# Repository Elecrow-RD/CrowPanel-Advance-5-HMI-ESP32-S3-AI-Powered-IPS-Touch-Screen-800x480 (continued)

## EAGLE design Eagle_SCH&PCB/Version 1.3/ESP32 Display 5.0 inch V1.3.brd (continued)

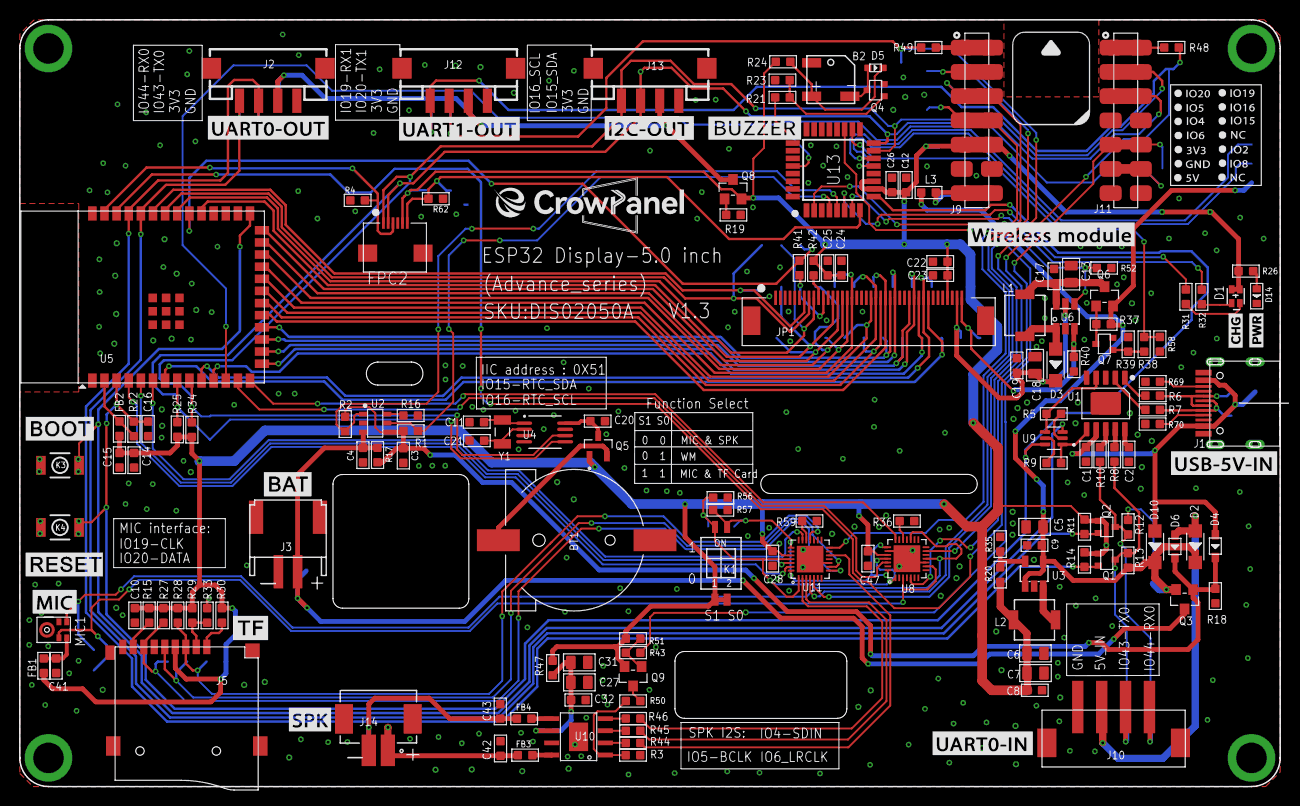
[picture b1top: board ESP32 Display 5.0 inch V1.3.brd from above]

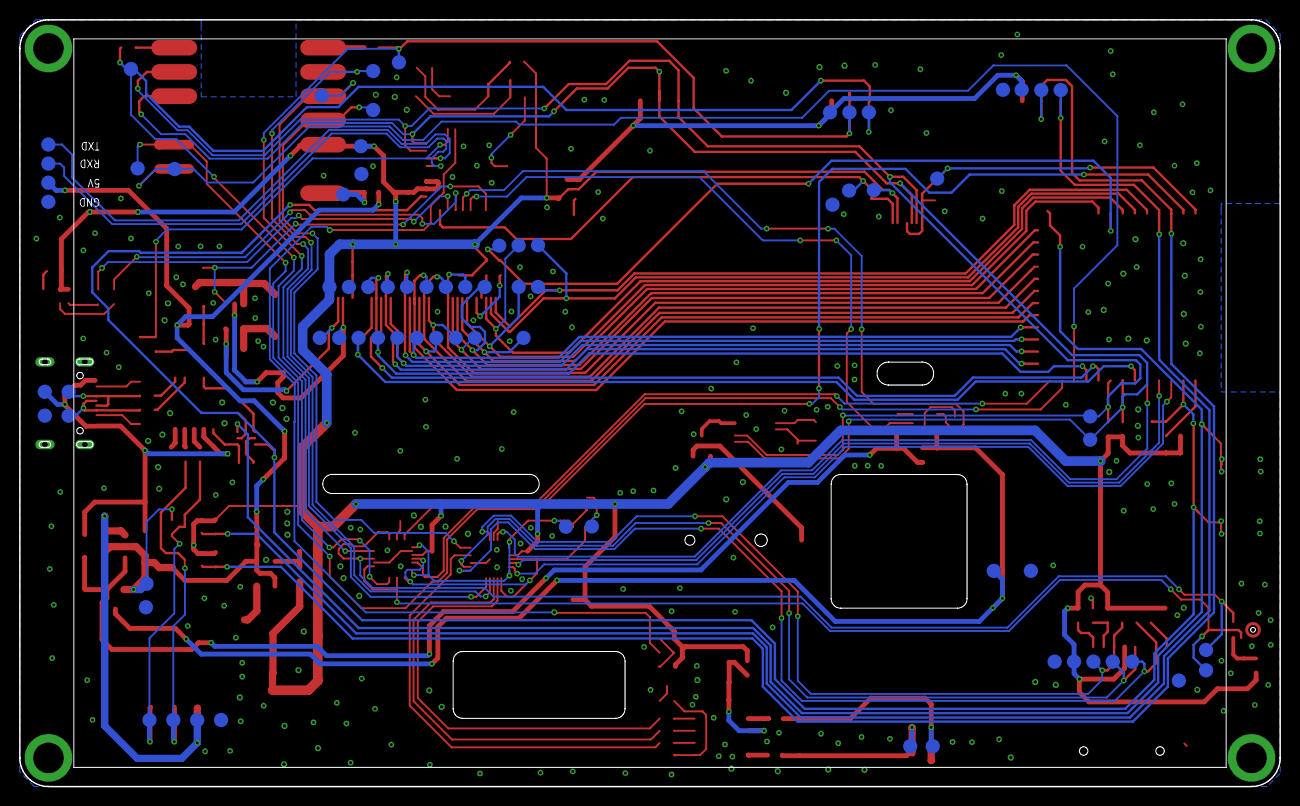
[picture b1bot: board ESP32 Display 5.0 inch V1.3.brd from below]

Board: 2 copper layers, 132.0 x 80.3 mm, 223 parts (72 on the bottom side), 126 nets.

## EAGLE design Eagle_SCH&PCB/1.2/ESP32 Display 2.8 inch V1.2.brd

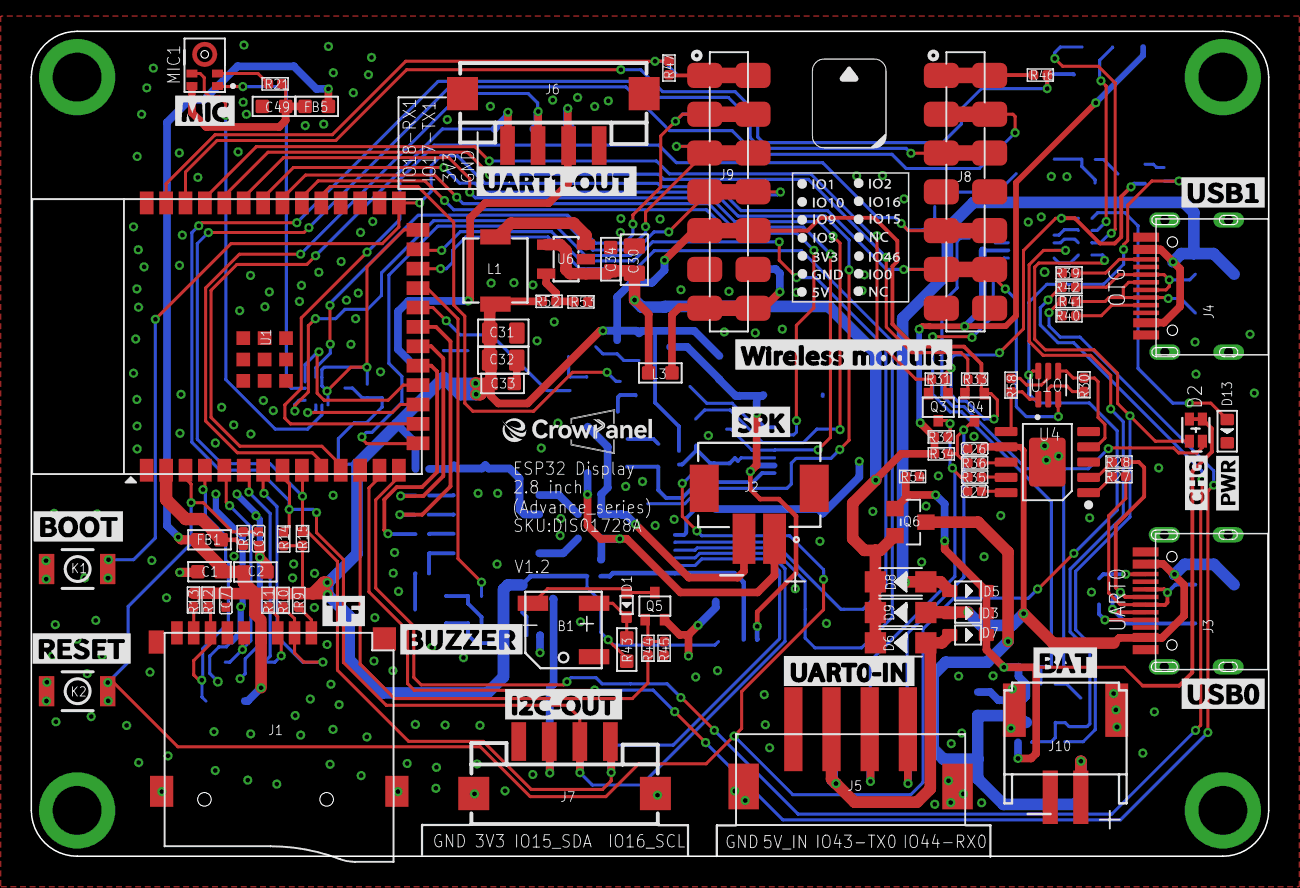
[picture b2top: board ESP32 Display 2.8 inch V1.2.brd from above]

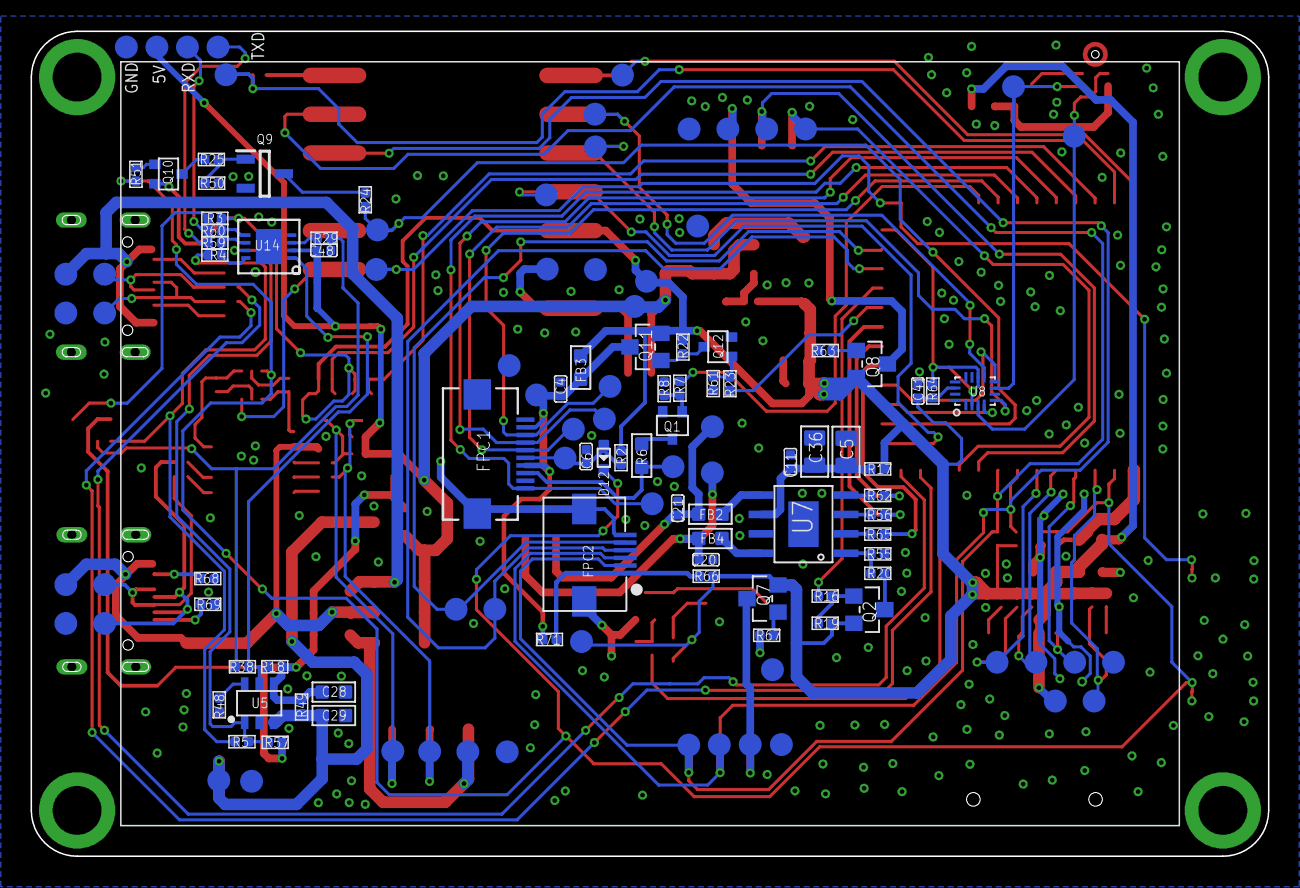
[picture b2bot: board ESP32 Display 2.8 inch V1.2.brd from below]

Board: 2 copper layers, 81.0 x 54.0 mm, 205 parts (124 on the bottom side), 117 nets.

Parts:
B1: BEEP_5025
C1: 10uF/0603; C0603
C2: 100nF/0603; C0603
C3, C6, C7, C26, C27, C41, C48: 1uF; C0402
C4, C11: 100nF; C0402
C5, C36: 47uF/0805; C0805
C20, C21: 1nF; C0402
C28, C33, C34: 1uF/0603; C0603
C29: 10uF/0603/NC; C0603
C30, C31, C32: 22uF/0805; C0805
C49: 100nF; C0603
D1, D12: B5819WT; D_SOD523
D2: KT-0603RYG; LED_KT-0603RYG
D3, D5, D7: 1N5817WS; D_SOD323
D6, D8, D9: DSS34; D_SOD123FL
D13: Red; LED0603
FB1, FB3, FB5: 0R/800mA; L0603
FB2, FB4: 1K/300mA; L0603
FPC1: TFT-2.4/2.8LCD-SPI-10P; FPC-P0.5MM-10P-SMD
FPC2: FPC-6PIN-0.5MMFPC-6PIN-0.5MM_2; FPC-6PIN-0.5MM_2
J1: 9P-SMD-W/-RING
J2: WAFER-PH2.0-2PLB; CONN-TH_2P-P2.00_XUNPU_WAFER-PH2.0-2PLB
J3, J4: TYPEC-3.0-16P-SMD; USB-3.0TYPEC-SMD
J5: XH2.54-4P-SMT; XH2.54-4P-SMD
J6, J7: HY2.0-4P-SMT; CONNECTOR_4P-SMD-2.0
J8, J9: H7-2.54-18.28X2.5X5MM
J10: PH2.0WT-2PIN
J11: HC-PZ200-8.7L-1X4PZ1; TEST-PIN-4-2.0MM
J12, J13, J14, J15: THO-M3.25MM-HOLE; THO-M3.2*5MM-HOLE
K1, K2: BUTTON; 157SW
L1: 4.7uH/3A; L0420
L3: NC; L0603
MIC1: LMD3526B261-OFA01; MIC-SMD_5P-L3.5-W2.7-P1.67
P1, P2, P3, P4, P5, P6, P7, P8, P9, P10, P11, P12, P13, P14, P15, P16, P17, P18, P19, P20, P21, P22, P23, P24, P26, P27, P28, P30, P31, P32, P34, P36, P37, P38, P39, P40, P41, P42, P43, P44, P45, P46, P47, P48, P49, P50, P51, P52, P53, P54, P55, P58, P59, P60, P61, P62: TEST_PADPAD-1.5MM; TEST_PAD-1.5MM
Q1, Q5: SS8050W-SOT323; MOS_SOT323
Q2, Q6, Q7, Q8: AO3401; PMOS_SOT23
Q3, Q4: BSS138W_SOT323; MOS_SOT323
Q9: AO3400A; SOT95P280X125-3N
Q10: SS8550W-SOT323; MOS_SOT323
Q11: AO3401/NC; PMOS_SOT23
Q12: SS8050W-SOT323//NC; MOS_SOT323
R1, R2, R9, R10, R11, R12, R13, R19, R30, R50, R51, R53, R54, R58, R63, R67: 10K; R0402
R3, R4, R18, R39, R40, R49, R57, R68, R69: 5.1K; R0402
R5, R38: NC; R0402
R6: 6.8R/0603; R0603-SP
R7, R20, R44: 1K; R0402
R8, R45: 47K; R0402
R14, R15, R31, R32, R33, R34: 4.7k; R0402
R16, R24, R25: 100R; R0402
R17, R27, R28, R35, R36, R41, R42, R46, R47, R56, R59, R60, R62, R65, R71: 0R; R0402
R21, R64: 10K/NC; R0402
R22: 100K/NC; R0402
R23: 1K/NC; R0402
R29, R48: 2K; R0402
R43: 3.9R/0603; R0603-SP
R52: 45.3K; R0402
R55: 100K; R0402
R61: 47K/NC; R0402
R66: 0R/NC; R0402
U1: ESP32-S3-WROOM-1; ESP32-S3-WROOM-1-SMD41
U4: CH340K; ESOP-10-EP-150MIL
U5: TP4059-SOT23-6; SOT23-6L
U6: RY3420; IC_SOT23-5
U7: NS4168-ESOP-8
U8: SGM3799; IC_SGM3799_TQFN2.6X1.8_16L
U10: UMH3NTN; SOP65P210X100-6N
U14: STC8G1K08; DFN8

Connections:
3V3: C1.2, C2.2, C7.2, C31.2, C32.2, C33.2, C41.2, FB1.1, FB3.1, FB5.1, J1.4, J9.5, J9.5-5, L1.2, P1.P$1, P17.P$1, P61.P$1, Q2.2, Q3.1, Q4.1, Q7.2, Q8.2, Q10.2, Q11.2, R2.2, R3.2, R9.2, R10.2, R11.2, R12.2, R13.2, R14.2, R15.2, R17.1, R19.2, R22.2, R31.2, R33.2, R43.2, R52.2, R64.2, R66.2, U8.14
3V3_1: C49.2, FB5.2, MIC1.4, R21.2
3V3_OUT1: J6.3, P36.P$1, Q8.3
3V3_OUT2: J7.3, P18.P$1, Q7.3
+5V_IN: D6.+, D7.+, J5.3, P40.P$1
+VBUS1: C26.2, D3.+, D9.+, J3.A4, J3.A9, J3.B4, J3.B9, P48.P$1, U4.7
+VBUS2: D5.+, D8.+, J4.A4, J4.A9, J4.B4, J4.B9, P44.P$1
+VC_IN: C28.2, D2.1, D2.2, D3.-, D5.-, D7.-, Q6.1, R18.1, R49.2, R54.2, R57.1, U5.4
CHRG: R5.1, R57.2, U5.1, U14.7
CH_EN: C3.2, D12.-, K2.2, R1.1, R51.1, U1.3, U10.6
C_LED: R4.1, U14.8
DA1: J1.8, R13.1
DA2: J1.1, R9.1
DONE: R18.2, R38.1, U5.5, U14.1
DTR: R30.2, U4.4, U10.4
D_LED: R29.1, U14.3
ESP_3V3: FB1.2, R1.2, U1.2
ESP_D+: R42.1, U1.14
ESP_D-: R41.1, U1.13
ESP_RXD0: Q4.2, R33.1, U1.36
ESP_RXD1: J6.1, P39.P$1, U1.11
ESP_RXD2: P58.P$1, R46.2, U1.38
ESP_TXD0: Q3.2, R31.1, U1.37
ESP_TXD1: J6.2, P38.P$1, U1.10
ESP_TXD2: P59.P$1, R47.2, U1.39
GND: C1.1, C2.1, C3.1, C4.1, C5.2, C6.1, C7.1, C11.2, C20.1, C21.1, C26.1, C27.1, C28.1, C29.1, C30.1, C31.1, C32.1, C33.1, C34.1, C36.2, C41.1, C48.1, C49.1, D13.-, FPC1.P$1, FPC1.P$11, FPC1.P$12, FPC2.6, FPC2.7, FPC2.8, J1.6, J1.G1, J1.G2, J1.G3, J1.G4, J2.3, J2.4, J3.A1, J3.A12, J3.B1, J3.B12, J3.P$1, J3.P$2, J3.P$3, J3.P$4, J4.A1, J4.A12, J4.B1, J4.B12, J4.P$1, J4.P$2, J4.P$3, J4.P$4, J5.4, J5.5, J5.6, J6.4, J6.SS1, J6.SS2, J7.4, J7.SS1, J7.SS2, J9.6, J9.6-6, J10.P$2, J10.P$3, J10.P$4, J11.4, J12.P$1, J13.P$1, J14.P$1, J15.P$1, K1.1, K2.1, MIC1.5_1, MIC1.5_2, P6.P$1, P16.P$1, P24.P$1, P34.P$1, P37.P$1, P41.P$1, P47.P$1, P51.P$1, P53.P$1, P55.P$1, P60.P$1, Q1.2, Q5.2, Q9.2, Q12.2, R8.2, R39.1, R40.1, R45.2, R48.1, R50.2, R53.1, R54.1, R55.2, R61.2, R63.1, R67.1, R68.1, R69.2, U1.1, U1.40, U1.41, U1.42, U1.43, U1.44, U1.45, U1.46, U1.47, U1.48, U1.49, U4.3, U4.EP, U5.2, U6.2, U7.7, U7.9, U8.6, U14.4, U14.P$9
IO0_W_CS: J8.6, J8.6-6, K1.2, P31.P$1, U1.27, U10.3
IO3_W_MOSI: J9.4, J9.4-4, P13.P$1, U1.15
IO4_SD_MISO: J1.7, P22.P$1, R12.1, U1.4
IO5_SD_SCK: J1.5, P21.P$1, U1.5
IO6_SD_MOSI: J1.3, P20.P$1, R11.1, U1.6
IO7_SD_CS: J1.2, P19.P$1, R10.1, U1.7
IO8_BEEP: R44.2, U1.12
IO9: U1.17, U8.4
IO9_MIC_CLK: MIC1.3, P27.P$1, U8.3
IO9_W_MISO: J9.3, J9.3-3, P14.P$1, U8.5
IO10: U1.18, U8.8
IO10_MIC_SD: MIC1.1, P26.P$1, U8.7
IO10_W_CLK: J9.2, J9.2-2, P23.P$1, U8.9
IO11_I2S_LRCLK: R65.2, U1.19
IO12_I2S_SDIN: R62.2, U1.20
IO13_I2S_BCLK: R56.2, U1.21
IO14_TFT_PWR: R23.2, U1.22
IO15_SDA: FPC2.3, J7.2, J8.3, J8.3-3, P2.P$1, R14.1, U1.8
IO16_SCL: FPC2.2, J7.1, J8.2, J8.2-2, P3.P$1, R15.1, U1.9
IO21_NS_CTRL: R16.1, U1.23
IO38_LED_BK: R7.2, U1.31
IO39_TFT_SDA: FPC1.P$3, P12.P$1, U1.32
IO40_TFT_CS: FPC1.P$5, P11.P$1, U1.33
IO41_TFT_RS: FPC1.P$10, P10.P$1, U1.34
IO42_TFT_SCK: FPC1.P$4, P9.P$1, U1.35
IO45_SPISW_ITCHING: R64.1, U1.26, U8.2, U8.10
IO46_BOOT_BUSY: J8.5, J8.5-5, P32.P$1, R24.2, U1.16
IO47_TP_INT: FPC2.4, P4.P$1, U1.24
IO48_TP_RST: FPC2.5, P5.P$1, U1.25
IOT_5V: J9.7, J9.7-7, L3.1, P62.P$1
LED_K: FPC1.P$8, P15.P$1, R6.2
unnamed: Q1.3, R6.1
unnamed: D13.+, R3.1
unnamed: Q1.1, R7.1, R8.1
unnamed: D2.3, R29.2, R38.2
unnamed: D2.4, R4.2, R5.2
unnamed: R20.2, R55.1, U7.1
unnamed: MIC1.2, R21.1
unnamed: R65.1, U7.2
unnamed: Q2.1, R16.2, R19.1
unnamed: Q12.1, R23.1, R61.1
unnamed: FPC2.1, R66.1, R71.1
unnamed: Q9.1, R25.1, R50.1
unnamed: Q10.3, R25.2
unnamed: R27.1, U4.1
unnamed: R28.1, U4.2
unnamed: L1.1, U6.3
unnamed: R30.1, U10.2
unnamed: R58.1, U10.5
unnamed: R59.2, U14.6
unnamed: C27.2, U4.10
unnamed: R60.2, U14.5
unnamed: R35.2, U4.9
unnamed: R36.2, U4.8
unnamed: J9.1, J9.1-1, R47.1
unnamed: J4.B5, R39.2
unnamed: J4.A5, R40.2
unnamed: Q5.1, R44.1, R45.1
unnamed: B1.2, D1.+, Q5.3
unnamed: B1.1, D1.-, R43.1
unnamed: Q10.1, R51.2
unnamed: R52.1, R53.2, U6.5
unnamed: R48.2, U5.6
unnamed: J3.A5, R69.1
unnamed: J3.B5, R68.2
unnamed: Q11.1, Q12.3, R22.1
unnamed: J8.1, J8.1-1, R46.1
unnamed: Q8.1, R63.2
unnamed: Q7.1, R67.2
unnamed: R56.1, U7.3
unnamed: R62.1, U7.4
unnamed: C5.1, C11.1, C36.1, R17.2, U7.6
unnamed: Q9.3, R24.1
NS_3V3: Q2.3, R20.1
OTG_D+: J4.A6, J4.B6, P46.P$1, R42.2
OTG_D-: J4.A7, J4.B7, P45.P$1, R41.2
ROUT+: C20.2, FB4.2, J2.1, P30.P$1
ROUT-: C21.2, FB2.2, J2.2, P28.P$1
RTS: R58.2, U4.6, U10.1
RXD: J11.2, R60.1
RXD0_H: J5.1, P43.P$1, Q4.3, R34.1, R36.1
TFT_3V3: C4.2, FB3.2, FPC1.P$2, FPC1.P$7, P7.P$1, Q11.3, R71.2
TFT_RST: C6.2, D12.+, FPC1.P$6, P8.P$1, R2.1
TXD: J11.1, R59.1
TXD0_H: J5.2, P42.P$1, Q3.3, R32.1, R35.1
USB_D+: J3.A6, J3.B6, P49.P$1, R27.2
USB_D-: J3.A7, J3.B7, P50.P$1, R28.2
VBAT: C29.2, J10.P$1, P52.P$1, Q6.3, R49.1, U5.3
VIN: C30.2, C34.2, C48.2, D6.-, D8.-, D9.-, J11.3, L3.2, P54.P$1, Q6.2, R32.2, R34.2, U6.1, U6.4, U14.2
VON: FB2.1, U7.5
VOP: FB4.1, U7.8

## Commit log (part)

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2026-04-10 Revise version table and update remarks
    Updated version table to reflect new versioning and remarks.
2026-04-22 sync example/V1.2
2026-05-10 sync example/V1.1
2026-06-03 libraries
2026-06-10 esp32
2026-06-15 remove libraries
2026-06-15 remove arduino
2026-06-15 rename folders for structure cleanup
2026-06-24 Thread
